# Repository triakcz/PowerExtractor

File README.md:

PowerExtractor
==============

GPL MPPT Regulator for bike (development prototype)

This is not finished project in development. Using Arduino to maximize power extracted from dynamo hub or solar panels ... yes it is so universal. Prototype tests shown power output of 8Watts @ 40km/h. Conversion efficiency is about 90% measured after initial rectification).

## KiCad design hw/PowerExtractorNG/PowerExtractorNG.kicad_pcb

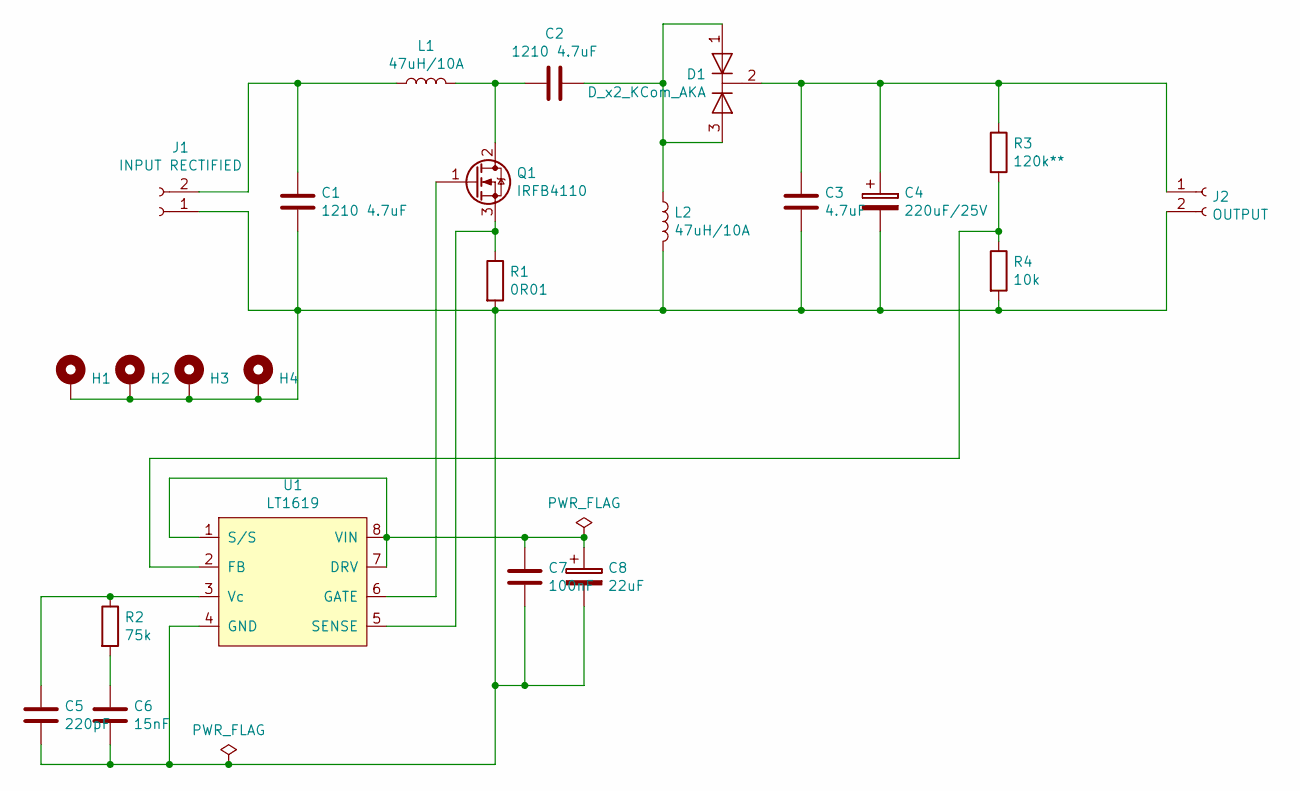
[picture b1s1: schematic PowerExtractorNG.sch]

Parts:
C1, C2: 1210 4.7uF; C_1210_3225Metric_Pad1.42x2.65mm_HandSolder
C3: 4.7uF; C_1210_3225Metric_Pad1.42x2.65mm_HandSolder
C4: 220uF/25V; CP_Radial_D10.0mm_P5.00mm
C5: 220pF; C_1206_3216Metric_Pad1.42x1.75mm_HandSolder
C6: 15nF; C_1206_3216Metric_Pad1.42x1.75mm_HandSolder
C7: 100nF; C_1206_3216Metric_Pad1.42x1.75mm_HandSolder
C8: 22uF; CP_Radial_D7.5mm_P2.50mm
D1: D_x2_KCom_AKA; TO-220-3_Vertical
H1, H2, H3, H4: MountingHole_Pad; MountingHole_3.2mm_M3_Pad
J1: INPUT RECTIFIED; TerminalBlock_Altech_AK300-2_P5.00mm
J2: OUTPUT; TerminalBlock_Altech_AK300-2_P5.00mm
L1, L2: 47uH/10A; L_Toroid_Vertical_L24.6mm_W15.5mm_P11.44mm_Pulse_KM-4
Q1: IRFB4110; TO-220-3_Vertical
R1: 0R01; R_2512_6332Metric_Pad1.52x3.35mm_HandSolder
R2: 75k; R_1206_3216Metric_Pad1.42x1.75mm_HandSolder
R3: 120k**; R_1206_3216Metric_Pad1.42x1.75mm_HandSolder
R4: 10k; R_1206_3216Metric_Pad1.42x1.75mm_HandSolder
U1: LT1619; SO-8_5.3x6.2mm_P1.27mm

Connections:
unnamed: C1.1, J1.2, L1.1
unnamed: C1.2, C3.2, C4.2, C5.2, C6.2, C7.2, C8.2, H1.1, H2.1, H3.1, H4.1, J1.1, J2.2, L2.2, R1.2, R4.2, U1.4 (GND)
unnamed: C2.1, D1.1 (A), D1.3 (A), L2.1
unnamed: C2.2, L1.2, Q1.2 (D)
unnamed: C3.1, C4.1, D1.2 (K), J2.1, R3.1
unnamed: C5.1, R2.1, U1.3 (Vc)
unnamed: C6.1, R2.2
unnamed: C7.1, C8.1, U1.1 (S/S), U1.7 (DRV), U1.8 (VIN)
unnamed: Q1.1 (G), U1.6 (GATE)
unnamed: Q1.3 (S), R1.1, U1.5 (SENSE)
unnamed: R3.2, R4.1, U1.2 (FB)

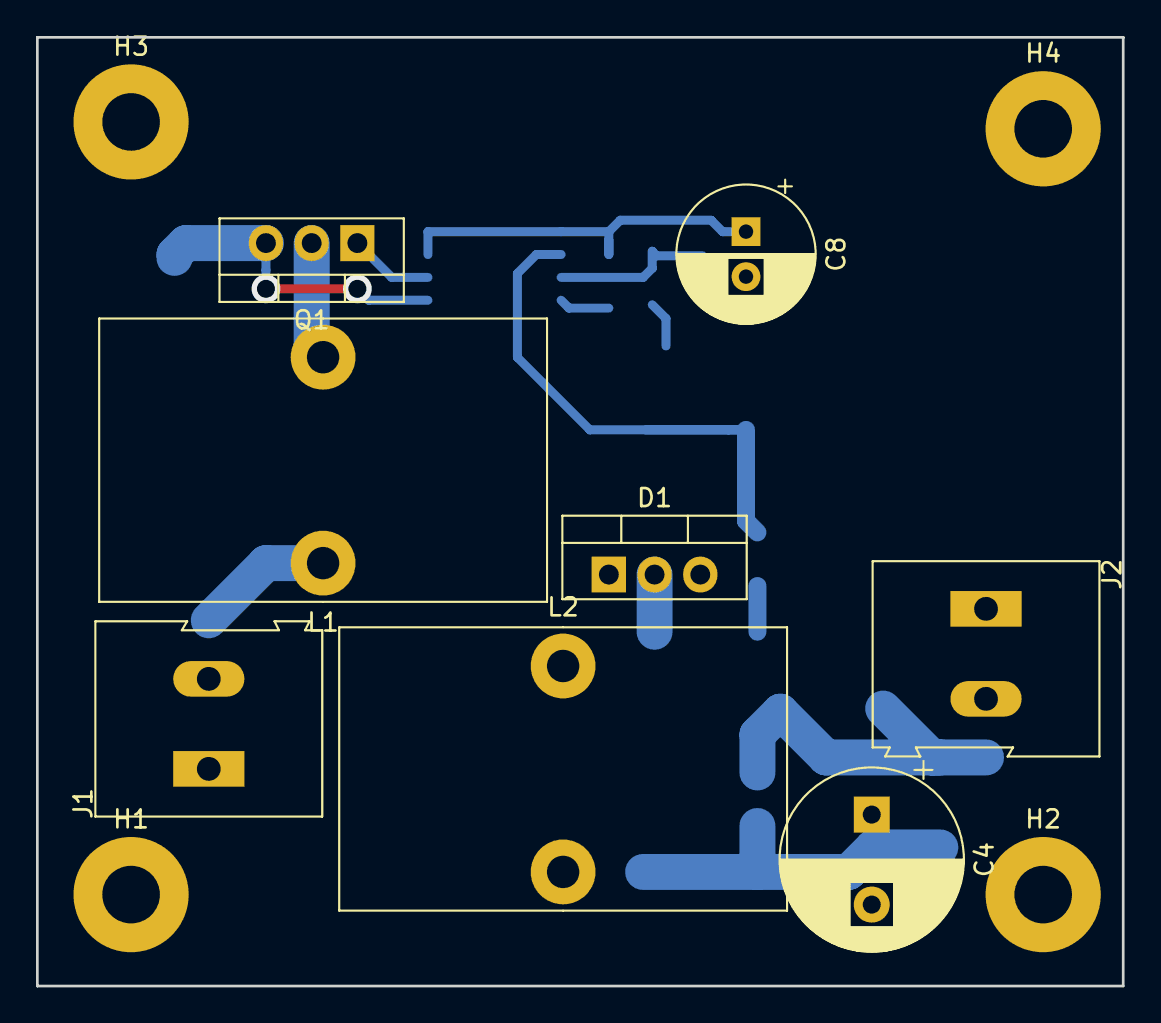
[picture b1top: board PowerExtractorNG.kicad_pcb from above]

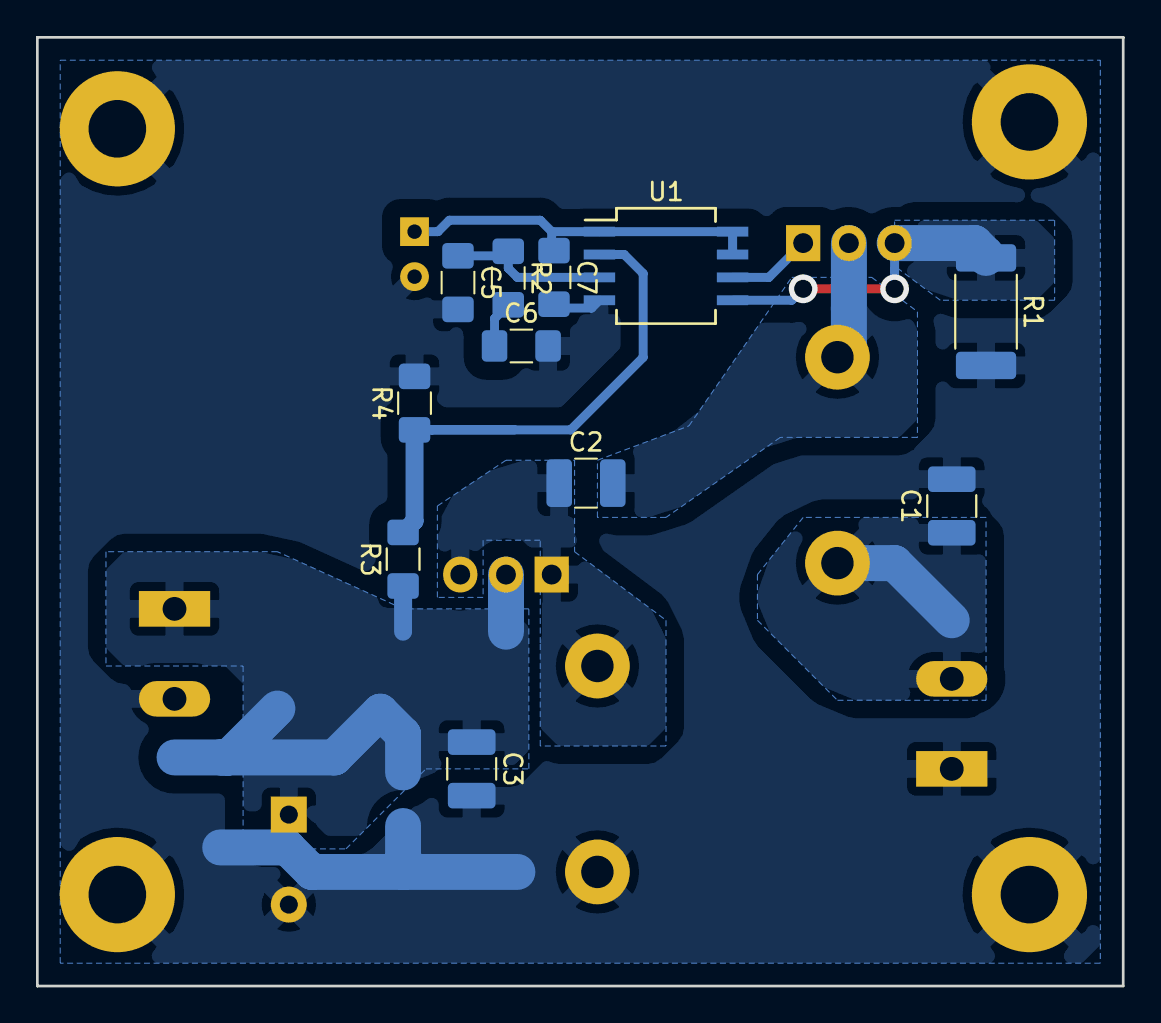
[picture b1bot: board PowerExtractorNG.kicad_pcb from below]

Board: 2 copper layers, 60.3 x 52.7 mm, 23 parts (11 on the bottom side), 11 nets.

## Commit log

2013-05-15 Description and license
2013-05-15 First version of prototype firmware
2013-05-15 First version of MPPT prototype
2013-05-16 Experimentally switching USB power output with NXP630AD2T by UP/DOWN keys
2015-06-21 Modifications of schematic and added library with components
2015-06-22 Add 5V USB out, 12V out, both controlled by arduino
2015-06-23 Arduino Nano V3 in library
2015-10-12 Connected arduino in schematic
2016-03-20 Adding latest version
2016-03-20 Routing of board
2016-03-20 Routing
2016-03-21 Refactored layout
2016-03-22 Completely routed
2016-03-23 set reasonable width of power lines
2016-04-03 Added spice netlist for new speedsense circuit
2016-04-05 Adding BCV47 to library
2016-04-05 Fixed speed sense circuit
2016-04-07 Shifted speed sense circuit under MCU
2016-04-07 Refactored PCB layout
2016-04-10 Added prefix to custom devices in eagle library
2016-04-10 Updated library - arduino removed holes from dimension layer
2016-04-10 Fixed upside down in layout2 cam job for PE
2016-04-10 layout2 fix
2016-04-11 Fixed values and types of few parts
2016-04-14 Fixed BSS84 pinout
2016-04-21 Multiple firmware parts
    - Manual PWM control
    - Voltage read and display functions
    - Keyboard handling method
    - Added interrupts for periodic actions
    - Turnofftimer skeleton
2016-04-21 Fixed wrongly placed resistor (0207 placed on bottom side)
2016-06-12 Fixing various bugs
2016-06-13 multiple fixes
2016-06-13 refactoring
2020-01-12 backup all
2020-01-12 wip kicad
2020-01-14 Done
2020-05-10 PE2020
